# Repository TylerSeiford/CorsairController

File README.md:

# CorsairController
This is the code and kicad files for my knock off Corsair CommanderPRO using an ATmega32u4 microcontroller.

## Hardware
This uses an ATmega32u4 microcontroller to control addressable and non addressable LED strips, along with 3 and 4 pin DC fans.  It utilizes the [CorsairLightingProtocol](https://github.com/Legion2/CorsairLightingProtocol) and builds on top of it to add additional functionality.

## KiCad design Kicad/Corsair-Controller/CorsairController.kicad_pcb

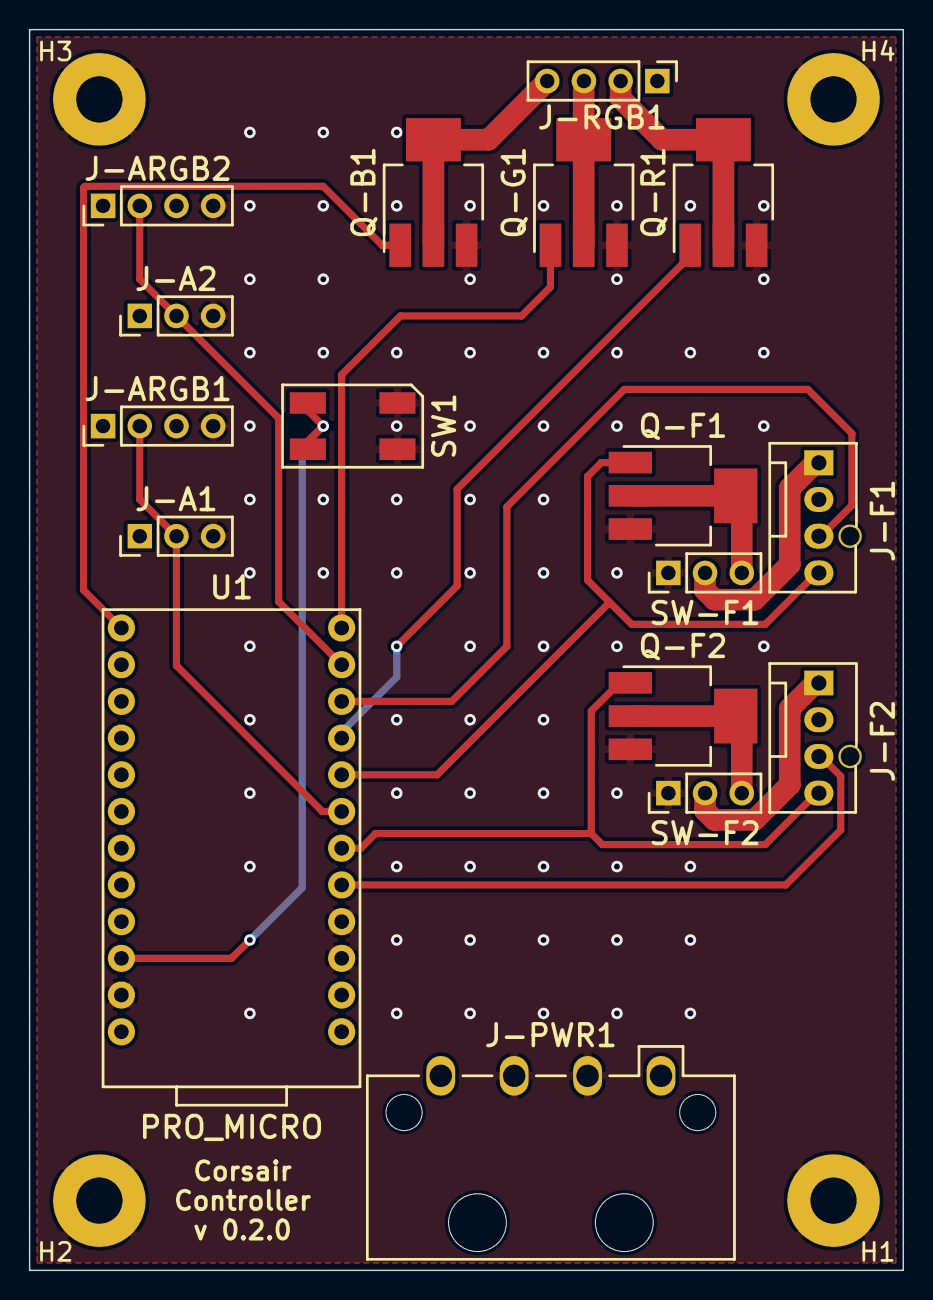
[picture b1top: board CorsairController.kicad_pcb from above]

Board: 2 copper layers, 60.5 x 85.9 mm, 21 parts (0 on the bottom side), 20 nets.

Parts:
H1, H2, H3, H4: MountingHole; MountingHole_3.2mm_M3_Pad
J-A1, J-A2: Conn_01x03_Male; PinHeader_1x03_P2.54mm_Vertical
J-ARGB1, J-ARGB2: Conn_01x04_Male; PinHeader_1x04_P2.54mm_Vertical
J-F1, J-F2: Conn_01x04_Male; 0470531000
J-PWR1: Conn_01x04_Female; 641737-1
J-RGB1: Conn_01x04_Male; PinHeader_1x04_P2.54mm_Vertical
Q-B1: Q_NMOS_GDSD; SOT-223
Q-F1, Q-F2: Q_NMOS_GDSD; SOT-223
Q-G1: Q_NMOS_GDSD; SOT-223
Q-R1: Q_NMOS_GDSD; SOT-223
SW1: RESET_SWITCH; PTS_647_SM38_SMTR2_LFS
SW-F1, SW-F2: SW_SPDT; PinHeader_1x03_P2.54mm_Vertical
U1: PRO_MICRO; SPARKFUN_PRO_MICRO

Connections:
/5V: J-ARGB1.1, J-ARGB2.1, J-PWR1.4
/12V: J-A1.1, J-A2.1, J-F1.2, J-F2.2, J-PWR1.1, J-RGB1.1
/A1: J-A1.2, J-ARGB1.2, U1.7
/A2: J-A2.2, J-ARGB2.2, U1.11
/B-5V: Q-B1.1, U1.13
/B-12V: J-RGB1.4, Q-B1.2, Q-B1.4
/F1-5V: J-F1.4, Q-F1.1, U1.8
/F1-12V: Q-F1.2, Q-F1.4, SW-F1.3
/F1-GND: J-F1.1, SW-F1.2
/F1-T: J-F1.3, U1.10
/F2-5V: J-F2.4, Q-F2.1, U1.6
/F2-12V: Q-F2.2, Q-F2.4, SW-F2.3
/F2-GND: J-F2.1, SW-F2.2
/F2-T: J-F2.3, U1.5
/G-5V: Q-G1.1, U1.12
/G-12V: J-RGB1.3, Q-G1.2, Q-G1.4
/R-5V: Q-R1.1, U1.9
/R-12V: J-RGB1.2, Q-R1.2, Q-R1.4
/RESET: SW1.2, SW1.4, U1.22
GND: H1.1, H2.1, H3.1, H4.1, J-A1.3, J-A2.3, J-ARGB1.4, J-ARGB2.4, J-PWR1.2, J-PWR1.3, Q-B1.3, Q-F1.3, Q-F2.3, Q-G1.3, Q-R1.3, SW1.1, SW1.3, SW-F1.1, SW-F2.1, U1.3, U1.4, U1.23

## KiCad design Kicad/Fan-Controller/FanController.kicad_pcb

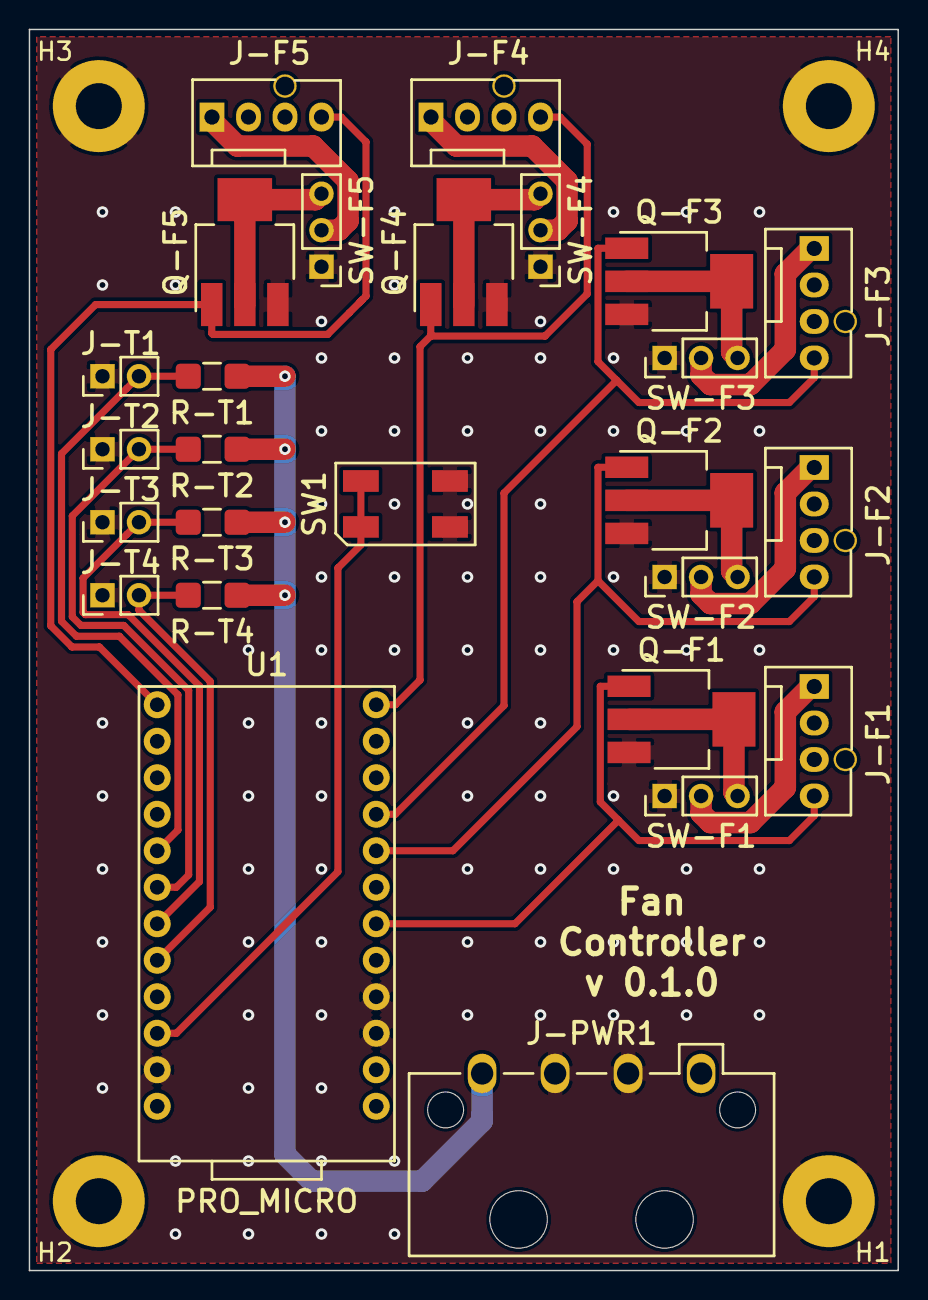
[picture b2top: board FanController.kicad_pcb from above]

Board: 2 copper layers, 60.5 x 86.4 mm, 30 parts (0 on the bottom side), 23 nets.

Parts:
H1, H2, H3, H4: MountingHole; MountingHole_3.2mm_M3_Pad
J-F1, J-F2, J-F3, J-F4, J-F5: Conn_01x04_Male; 0470531000
J-PWR1: Conn_01x04_Female; 641737-1
J-T1, J-T2, J-T3, J-T4: Conn_01x02_Male; PinHeader_1x02_P2.54mm_Vertical
Q-F1, Q-F2, Q-F3, Q-F4, Q-F5: Q_NMOS_GDSD; SOT-223
R-T1, R-T2, R-T3, R-T4: R; R_1206_3216Metric_Pad1.42x1.75mm_HandSolder
SW1: RESET_SWITCH; PTS_647_SM38_SMTR2_LFS
SW-F1, SW-F2, SW-F3, SW-F4, SW-F5: SW_SPDT; PinHeader_1x03_P2.54mm_Vertical
U1: PRO_MICRO; SPARKFUN_PRO_MICRO

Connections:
/5V: J-PWR1.4, R-T1.2, R-T2.2, R-T3.2, R-T4.2
/12V: J-F1.2, J-F2.2, J-F3.2, J-F4.2, J-F5.2, J-PWR1.1
/F1-5V: J-F1.4, Q-F1.1, U1.6
/F1-12V: Q-F1.2, Q-F1.4, SW-F1.3
/F1-GND: J-F1.1, SW-F1.2
/F2-5V: J-F2.4, Q-F2.1, U1.8
/F2-12V: Q-F2.2, Q-F2.4, SW-F2.3
/F2-GND: J-F2.1, SW-F2.2
/F3-5V: J-F3.4, Q-F3.1, U1.9
/F3-12V: Q-F3.2, Q-F3.4, SW-F3.3
/F3-GND: J-F3.1, SW-F3.2
/F4-5V: J-F4.4, Q-F4.1, U1.12
/F4-12V: Q-F4.2, Q-F4.4, SW-F4.3
/F4-GND: J-F4.1, SW-F4.2
/F5-5V: J-F5.4, Q-F5.1, U1.13
/F5-12V: Q-F5.2, Q-F5.4, SW-F5.3
/F5-GND: J-F5.1, SW-F5.2
/RESET: SW1.1, SW1.3, U1.22
/T1: J-T1.2, R-T1.1, U1.17
/T2: J-T2.2, R-T2.1, U1.18
/T3: J-T3.2, R-T3.1, U1.19
/T4: J-T4.2, R-T4.1, U1.20
GND: H1.1, H2.1, H3.1, H4.1, J-PWR1.2, J-PWR1.3, J-T1.1, J-T2.1, J-T3.1, J-T4.1, Q-F1.3, Q-F2.3, Q-F3.3, Q-F4.3, Q-F5.3, SW1.2, SW1.4, SW-F1.1, SW-F2.1, SW-F3.1, SW-F4.1, SW-F5.1, U1.3, U1.4, U1.23

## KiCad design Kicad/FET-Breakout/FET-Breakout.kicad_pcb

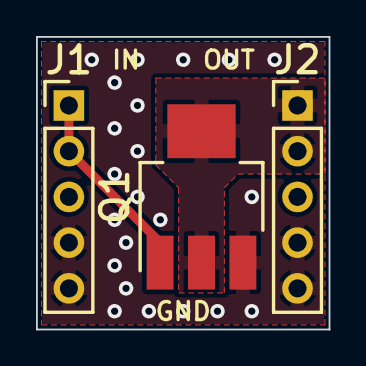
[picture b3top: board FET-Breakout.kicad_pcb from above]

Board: 2 copper layers, 16.3 x 16.3 mm, 3 parts (0 on the bottom side), 3 nets.

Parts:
J1, J2: Conn_01x05_Male; PinHeader_1x05_P2.54mm_Vertical
Q1: Q_NMOS_GDSD; SOT-223

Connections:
/GATE: J1.1, J1.2, Q1.1
/GND: J1.4, J1.5, J2.4, J2.5, Q1.3
/OUT: J2.1, J2.2, Q1.2, Q1.4

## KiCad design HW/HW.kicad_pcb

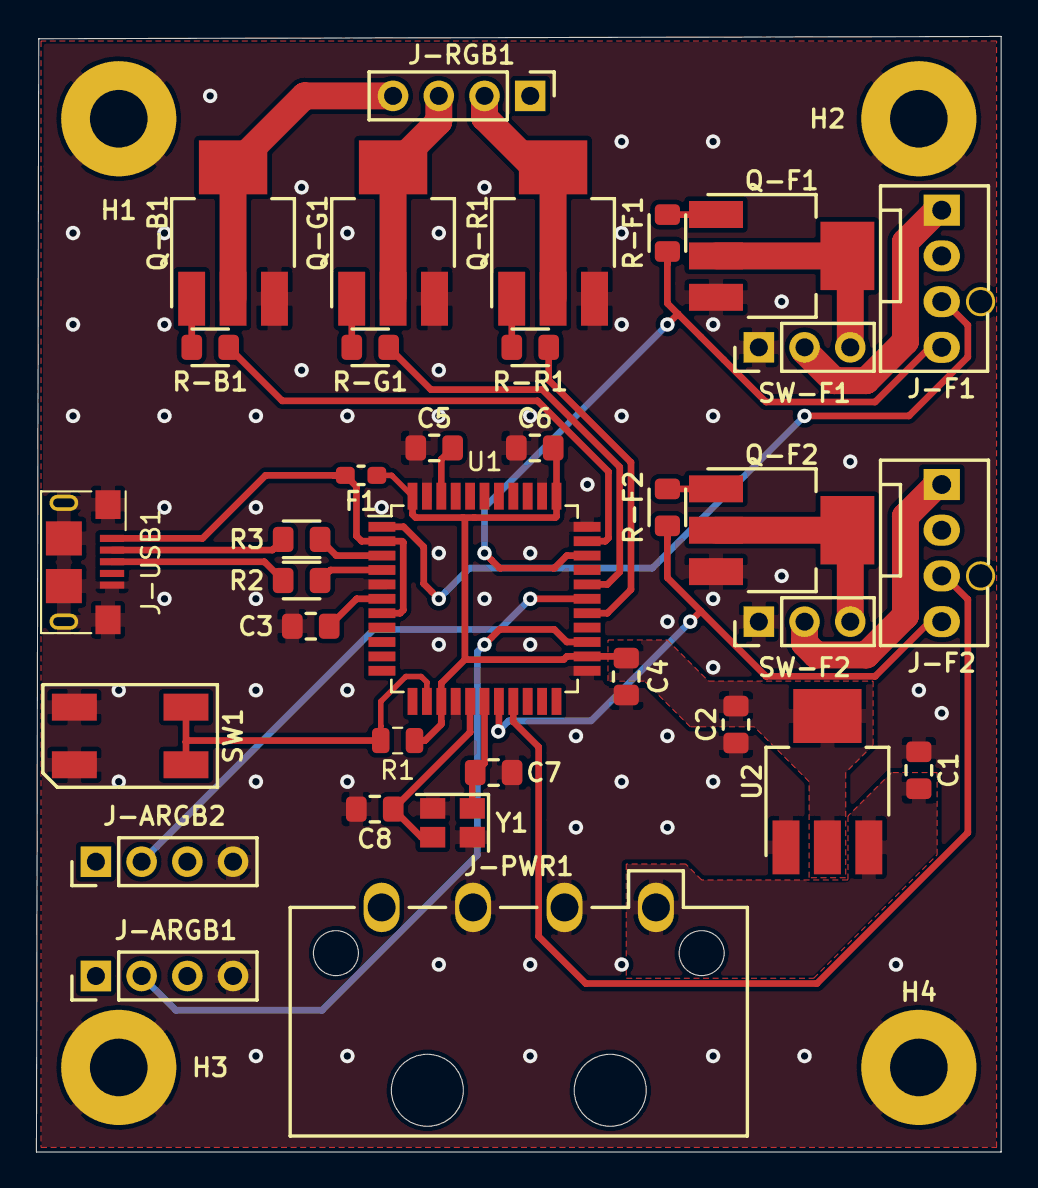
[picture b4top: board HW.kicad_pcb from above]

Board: 2 copper layers, 53.6 x 62.0 mm, 39 parts (0 on the bottom side), 35 nets.

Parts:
C1, C2: 10uF; C_0805_2012Metric_Pad1.15x1.40mm_HandSolder
C3, C4: 1uF; C_0805_2012Metric_Pad1.15x1.40mm_HandSolder
C5, C6: 0.1uF; C_0805_2012Metric_Pad1.15x1.40mm_HandSolder
C7, C8: 22pF; C_0805_2012Metric_Pad1.15x1.40mm_HandSolder
F1: Polyfuse; Fuse_0603_1608Metric_Pad1.05x0.95mm_HandSolder
H1, H2, H3, H4: MountingHole; MountingHole_3.2mm_M3_Pad
J-ARGB1, J-ARGB2: Conn_01x04_Male; PinHeader_1x04_P2.54mm_Vertical
J-F1, J-F2: Conn_01x04_Male; 0470531000
J-PWR1: Conn_01x04_Female; 641737-1
J-RGB1: Conn_01x04_Male; PinHeader_1x04_P2.54mm_Vertical
J-USB1: USB_B_Micro; USB_Micro-B
Q-B1: Q_NMOS_GDSD; SOT-223
Q-F1, Q-F2: Q_NMOS_GDSD; SOT-223
Q-G1: Q_NMOS_GDSD; SOT-223
Q-R1: Q_NMOS_GDSD; SOT-223
R1: 10k; R_0805_2012Metric
R2, R3: 22; R_0805_2012Metric_Pad1.15x1.40mm_HandSolder
R-B1: 10; R_0805_2012Metric_Pad1.15x1.40mm_HandSolder
R-F1, R-F2: 10; R_0805_2012Metric_Pad1.15x1.40mm_HandSolder
R-G1: 10; R_0805_2012Metric_Pad1.15x1.40mm_HandSolder
R-R1: 10; R_0805_2012Metric_Pad1.15x1.40mm_HandSolder
SW1: RESET_SWITCH; PTS_647_SM38_SMTR2_LFS
SW-F1, SW-F2: SW_SPDT; PinHeader_1x03_P2.54mm_Vertical
U1: ATmega32U4-AU; TQFP-44_10x10mm_P0.8mm
U2: SPX1117; SOT-223
Y1: Crystal_GND24; Crystal_SMD_SeikoEpson_TSX3225-4Pin_3.2x2.5mm

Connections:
/5V: J-ARGB1.1, J-ARGB2.1, J-PWR1.4
/B: Q-B1.1, R-B1.2
/B-12V: J-RGB1.4, Q-B1.2, Q-B1.4
/F1: Q-F1.1, R-F1.2
/F1-12V: Q-F1.2, Q-F1.4, SW-F1.3
/F1-GND: J-F1.1, SW-F1.2
/F2: Q-F2.1, R-F2.2
/F2-12V: Q-F2.2, Q-F2.4, SW-F2.3
/F2-GND: J-F2.1, SW-F2.2
/G: Q-G1.1, R-G1.2
/G-12V: J-RGB1.3, Q-G1.2, Q-G1.4
/Microcontroller/AREF: C5.1, U1.42
/Microcontroller/D+: R2.1, U1.4
/Microcontroller/D+USB: J-USB1.3, R2.2
/Microcontroller/D-: R3.2, U1.3
/Microcontroller/D-USB: J-USB1.2, R3.1
/Microcontroller/UCAP: C3.1, U1.6
/Microcontroller/UVCC: F1.2, J-USB1.1, U1.2, U1.7
/Microcontroller/XTAL1: C7.1, U1.17, Y1.1
/Microcontroller/XTAL2: C8.1, U1.16, Y1.3
/R: Q-R1.1, R-R1.2
/R-12V: J-RGB1.2, Q-R1.2, Q-R1.4
D2: J-F2.3, U1.19
D3: J-F2.4, R-F2.1, U1.18
D4: J-ARGB1.2, U1.25
D5: J-F1.4, R-F1.1, U1.31
D6: R-R1.1, U1.27
D7: J-F1.3, U1.1
D8: J-ARGB2.2, U1.28
D9: R-G1.1, U1.29
D13: R-B1.1, U1.32
GND: C1.1, C2.1, C3.2, C4.1, C5.2, C6.1, C7.2, C8.2, H1.1, H2.1, H3.1, H4.1, J-ARGB1.4, J-ARGB2.4, J-PWR1.2, J-PWR1.3, J-USB1.5, J-USB1.6, Q-B1.3, Q-F1.3, Q-F2.3, Q-G1.3, Q-R1.3, SW1.1, SW1.3, SW-F1.1, SW-F2.1, U1.5, U1.15, U1.23, U1.33, U1.35, U1.43, U2.1, Y1.2, Y1.4
RAW: C1.2, J-F1.2, J-F2.2, J-PWR1.1, J-RGB1.1, U2.3
RESET: R1.2, SW1.2, SW1.4, U1.13
VCC: C2.2, C4.2, C6.2, F1.1, R1.1, U1.14, U1.24, U1.34, U1.44, U2.2, U2.4

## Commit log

2019-06-04 Basic lighting node pro class
2019-06-08 Added fritzing files
2019-06-11 Wiring update
2019-06-20 Rename files
2019-06-20 Change pins
2019-06-20 Creating fake temperature controller
2019-06-20 PWM fan
2019-06-20 Simple fan controller
2019-06-20 Commander pro updates
2019-06-20 Inline default update rate
2019-06-20 Update ino
2019-06-20 Fan interface update
2019-06-20 Add fan control to commander pro
2019-06-20 Fix board.txt to commander pro IDs
2019-06-20 Fix detection types
2019-06-20 Working fan control
2019-06-21 Switch to a template system
2019-06-21 Create DC fan
2019-06-22 Updated wiring to dual controller layout
    The second controller is unneeded at the moment but may become useful for full fan control
2019-06-23 Switching to eagle
2019-06-23 Added schematic and board images
2019-08-15 Pin changes, fixing template issues, added switches for 3 or 4 pin mode
2019-08-15 Last eagle revision & updated readme
2019-08-15 Removed eagle & fritzing, updated gitignore for KiCad
2019-08-15 PCB v0.1.0
    Initial kicad upload. This PCB has been a WIP for a while and this is the first time I've uploaded it to github.
2019-08-15 PCB v0.1.1
2019-08-15 PCB v0.1.2
2019-08-15 PCB v0.1.3
    Fixes fan header pinouts
2019-08-15 Redo PCB layout to be more efficient.
2019-08-15 Fix upload
2019-08-15 PCB v0.1.4
    Upload gerbers of first production run!
2019-08-18 Added LICENSE
2019-08-18 Small updates & added photos
2019-08-23 Update software to new CLP library version
2019-08-23 PCB v0.1.5
2019-08-24 Final updates of 2f/2x2argb/1rgb
2019-08-24 Small edits
2019-08-24 Starts of full fan control module
2019-08-24 Fan board is partially complete
2019-08-25 PCB v0.1.6
    Next step will be a complete reorganization of the PCB
2019-08-25 PCB v0.1.7
2019-08-25 Adding SOT-223 footprint from master
2019-08-25 Fan controller v0.0.2
2019-08-25 Fan PCB v0.0.3
2019-08-27 Fan PCB v0.0.4
    Switched to a molex screw terminal input
2019-08-27 PCB v0.1.8
    Switched to a molex screw terminal input
2019-08-27 Moved files
2019-08-27 Cleaned up the merge
2019-08-27 Added molex power input
2019-08-27 Fan PCB v0.0.5
2019-08-27 PCB v0.1.9
2019-08-27 PCB v0.1.9 (reupload)
2019-08-27 Fan PCB v0.0.6
2019-08-28 PCB v0.1.10
2019-08-29 Added reset button footprint & symbol
2019-08-29 PCB v0.1.11
2019-08-29 Fan PCB v0.0.7
2019-08-29 Renaming footprints
2019-08-29 Updated main PCB with new footprint names
2019-08-29 Rename and update fan PCB
2019-08-31 Switch to WS2112B strips
2019-08-31 Fix footprint to be 3"x2"
2019-10-01 Small updates
2019-10-18 Change resistors to 1206 from 0805
    Fan control v0.0.8
2019-11-09 Controller rev 0.2.0
2019-11-09 Remove gerbers
2019-11-09 FanController rev 0.1.0
2019-11-10 Added FET-Breakout PCB
2019-12-16 Moving to bare ATmega32U4 vs Pro Micro
2019-12-21 Small cleanup
2019-12-28 PCB v0.2.2
    Small cleanup, silkscreen work. Still need to do reset button.
2019-12-28 Cleanup of files
2019-12-28 Moved Software into SW folder
2019-12-28 Move KiCad files
2020-01-01 v0.2.5
    Serial number location
2020-01-03 v0.3.0
